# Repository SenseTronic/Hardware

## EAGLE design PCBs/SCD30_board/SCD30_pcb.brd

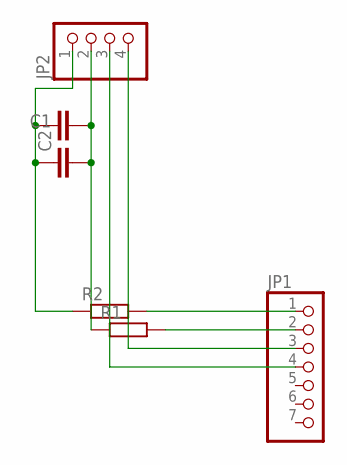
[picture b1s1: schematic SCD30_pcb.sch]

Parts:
C1: C2,5-3; C2.5-3
C2: C5/2.5; C5B2.5
JP1: PINHD-1X7; 1X07
JP2: PINHD-1X4/90; 1X04/90
R1, R2: R-EU_0204/7; 0204/7

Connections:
unnamed: JP1.3, JP2.4
unnamed: JP1.4, JP2.3
unnamed: JP1.2, R1.2
unnamed: JP1.1, R2.2
unnamed: C1.2, C2.2, JP2.2, R1.1
unnamed: C1.1, C2.1, JP2.1, R2.1

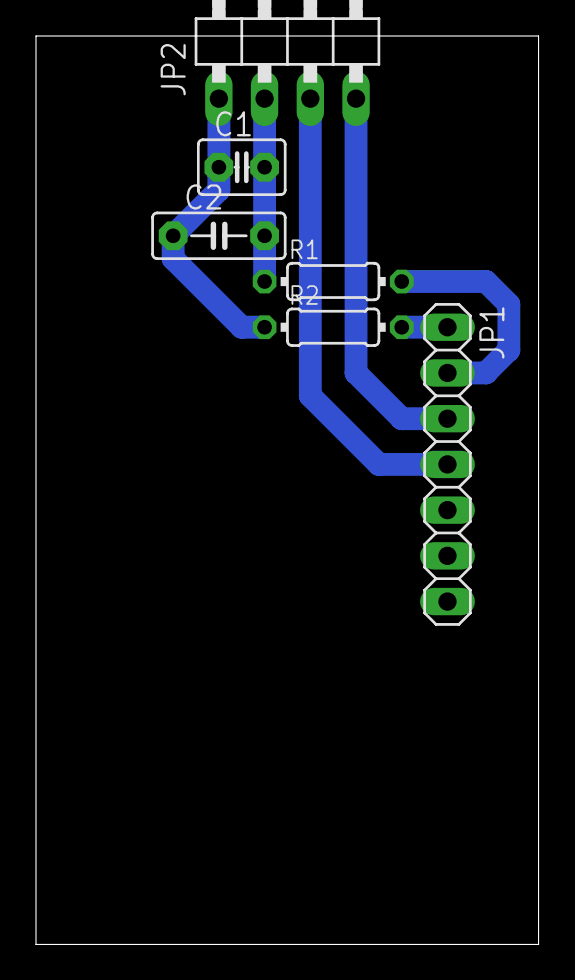
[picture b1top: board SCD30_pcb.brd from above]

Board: 2 copper layers, 27.9 x 50.5 mm, 6 parts (0 on the bottom side), 6 nets.

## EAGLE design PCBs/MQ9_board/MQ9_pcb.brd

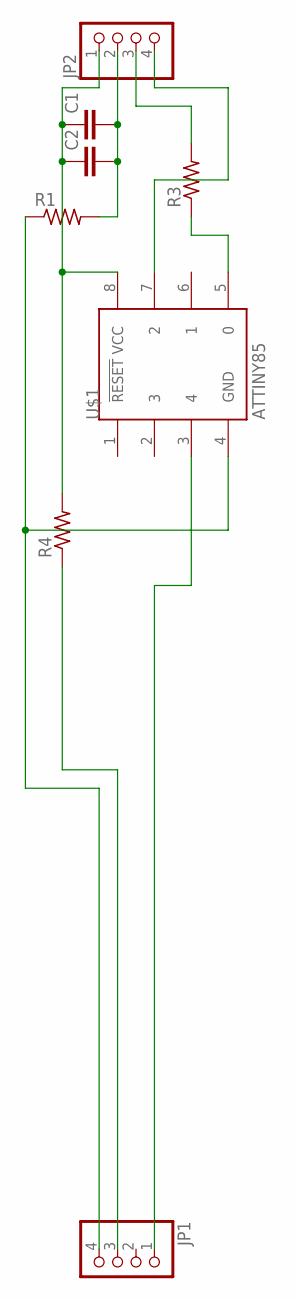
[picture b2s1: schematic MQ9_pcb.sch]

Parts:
C1: C2,5-3; C2.5-3
C2: C5/2.5; C5B2.5
JP1: PINHD-1X4; 1X04
JP2: PINHD-1X4/90; 1X04/90
R1, R3, R4: R-US_0204/5; 0204/5
U$1: ATTINY85; 8P3

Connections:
unnamed: C1.2, C2.2, JP2.2, R1.2
unnamed: C1.1, C2.1, JP2.1, R4.2, U$1.8 (VCC)
unnamed: JP1.4, R1.1, U$1.4 (GND)
unnamed: R3.1, U$1.5 (0)
unnamed: JP2.3, R3.2
unnamed: JP2.4, U$1.7 (2)
unnamed: JP1.1, U$1.3 (4)
unnamed: JP1.3, R4.1

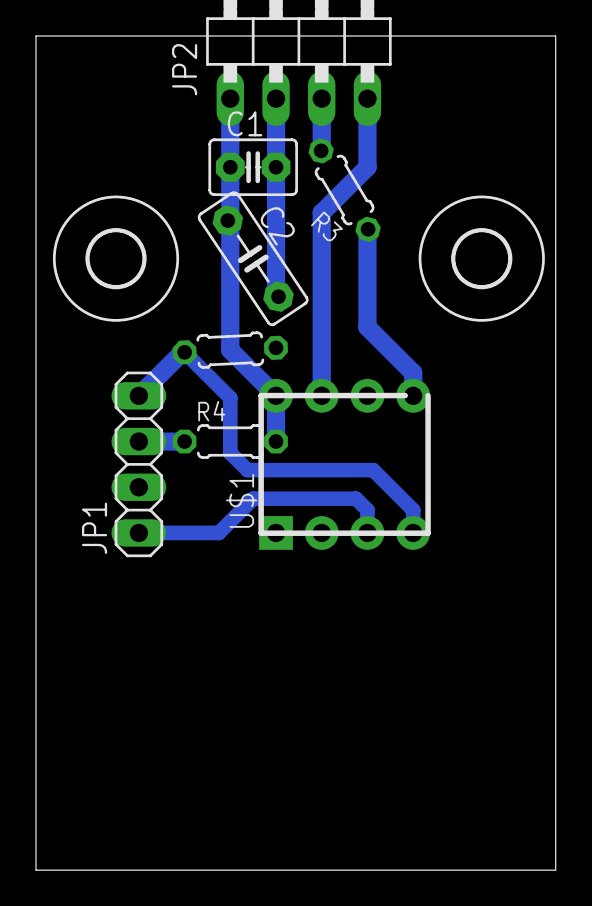
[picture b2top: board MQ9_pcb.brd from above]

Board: 2 copper layers, 28.9 x 46.3 mm, 10 parts (0 on the bottom side), 8 nets.

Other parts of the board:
U$2, U$3: 3,0

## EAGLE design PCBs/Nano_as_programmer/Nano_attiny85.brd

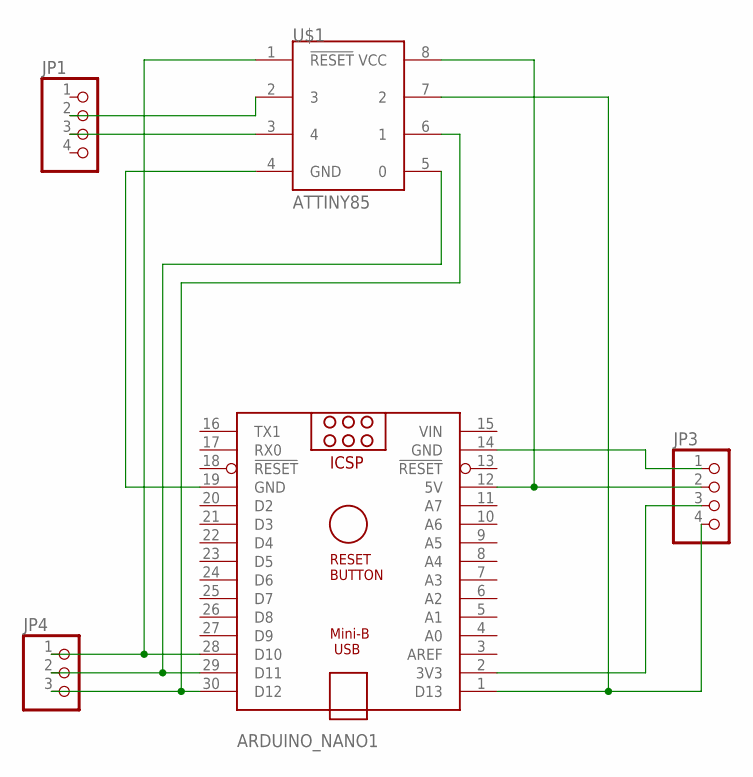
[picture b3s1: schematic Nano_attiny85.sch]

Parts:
ARDUINO_NANO1: ARDUINO_NANO
JP1, JP3: PINHD-1X4; 1X04
JP4: PINHD-1X3; 1X03
U$1: ATTINY85; 8P3

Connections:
unnamed: ARDUINO_NANO1.28 (D10), JP4.1, U$1.1 (!RESET)
unnamed: ARDUINO_NANO1.1 (D13), JP3.4, U$1.7 (2)
unnamed: ARDUINO_NANO1.29 (D11), JP4.2, U$1.5 (0)
unnamed: ARDUINO_NANO1.30 (D12), JP4.3, U$1.6 (1)
unnamed: ARDUINO_NANO1.12 (5V), JP3.2, U$1.8 (VCC)
unnamed: ARDUINO_NANO1.19 (GND), U$1.4 (GND)
unnamed: ARDUINO_NANO1.14 (GND), JP3.1
unnamed: JP1.3, U$1.3 (4)
unnamed: JP1.2, U$1.2 (3)
unnamed: ARDUINO_NANO1.2 (3V3), JP3.3
VIN: ARDUINO_NANO1.15 (VIN)

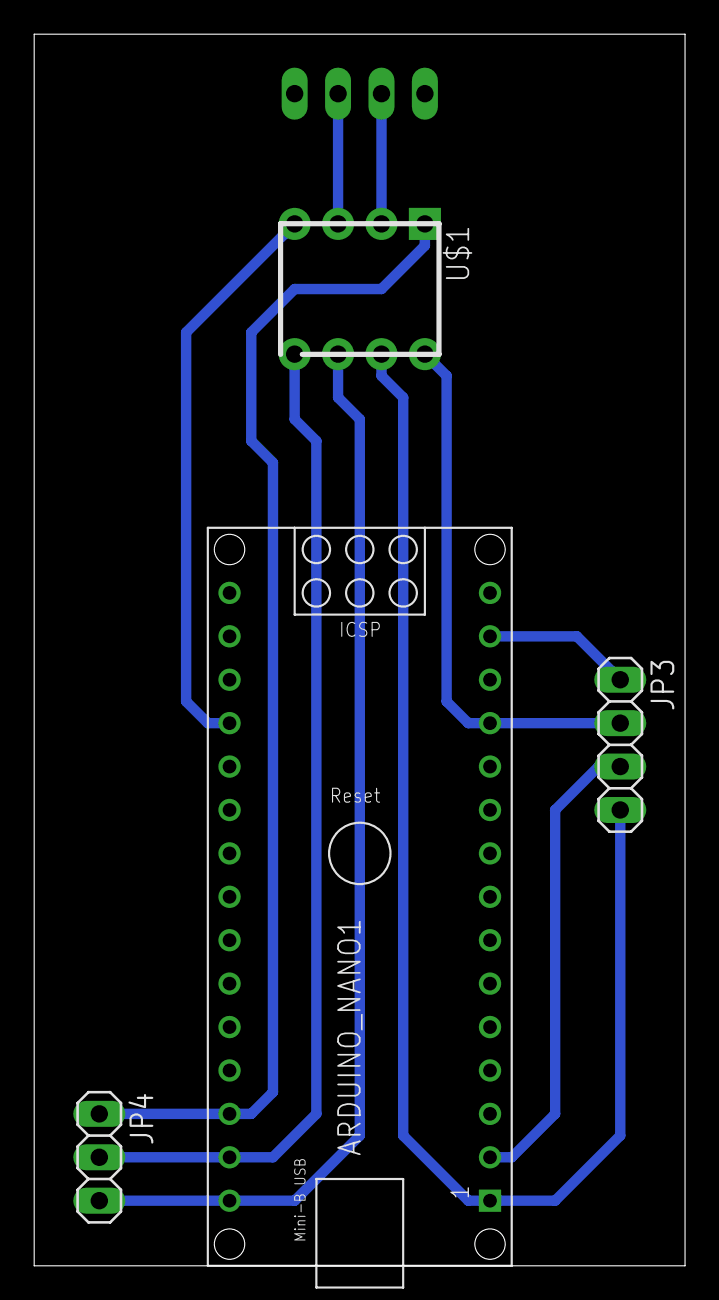
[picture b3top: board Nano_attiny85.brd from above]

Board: 2 copper layers, 38.1 x 72.1 mm, 5 parts (1 on the bottom side), 10 nets.

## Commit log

2020-01-26 Sensors_Tests
2020-01-26 Uma alteração para testar
2020-01-27 testing permissions
2020-01-27 removed useless teste.txt file
2020-03-15 Add CO conversion stuff
2020-03-27 Added Nano as attiny85 programmer PCB
2020-03-27 Added MQ9 PCB
2020-04-01 Added SCD30 PCB
2020-04-19 Codigo para calibração do MQ9 e conversão para ppms
2020-04-28 added bme680 pcb, still needs testing
2020-04-28 added bme680 pcb simulations
2020-05-16 added CU board
2020-05-16 organization of CU board folder
2020-05-20 added TSL2561 board
2020-05-20 added sensebox board
2020-06-04 added gerbers
